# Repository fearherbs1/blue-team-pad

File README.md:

# blue-team-pad
An open source macropad for the cyber security analyst.

View the documentation for the Blue Team Pad by visiting: https://fearherbs1.github.io/blue-team-pad-docs/

Below is the demo unit that was shown at Champlain's 2023 ITS Capstone Showcase

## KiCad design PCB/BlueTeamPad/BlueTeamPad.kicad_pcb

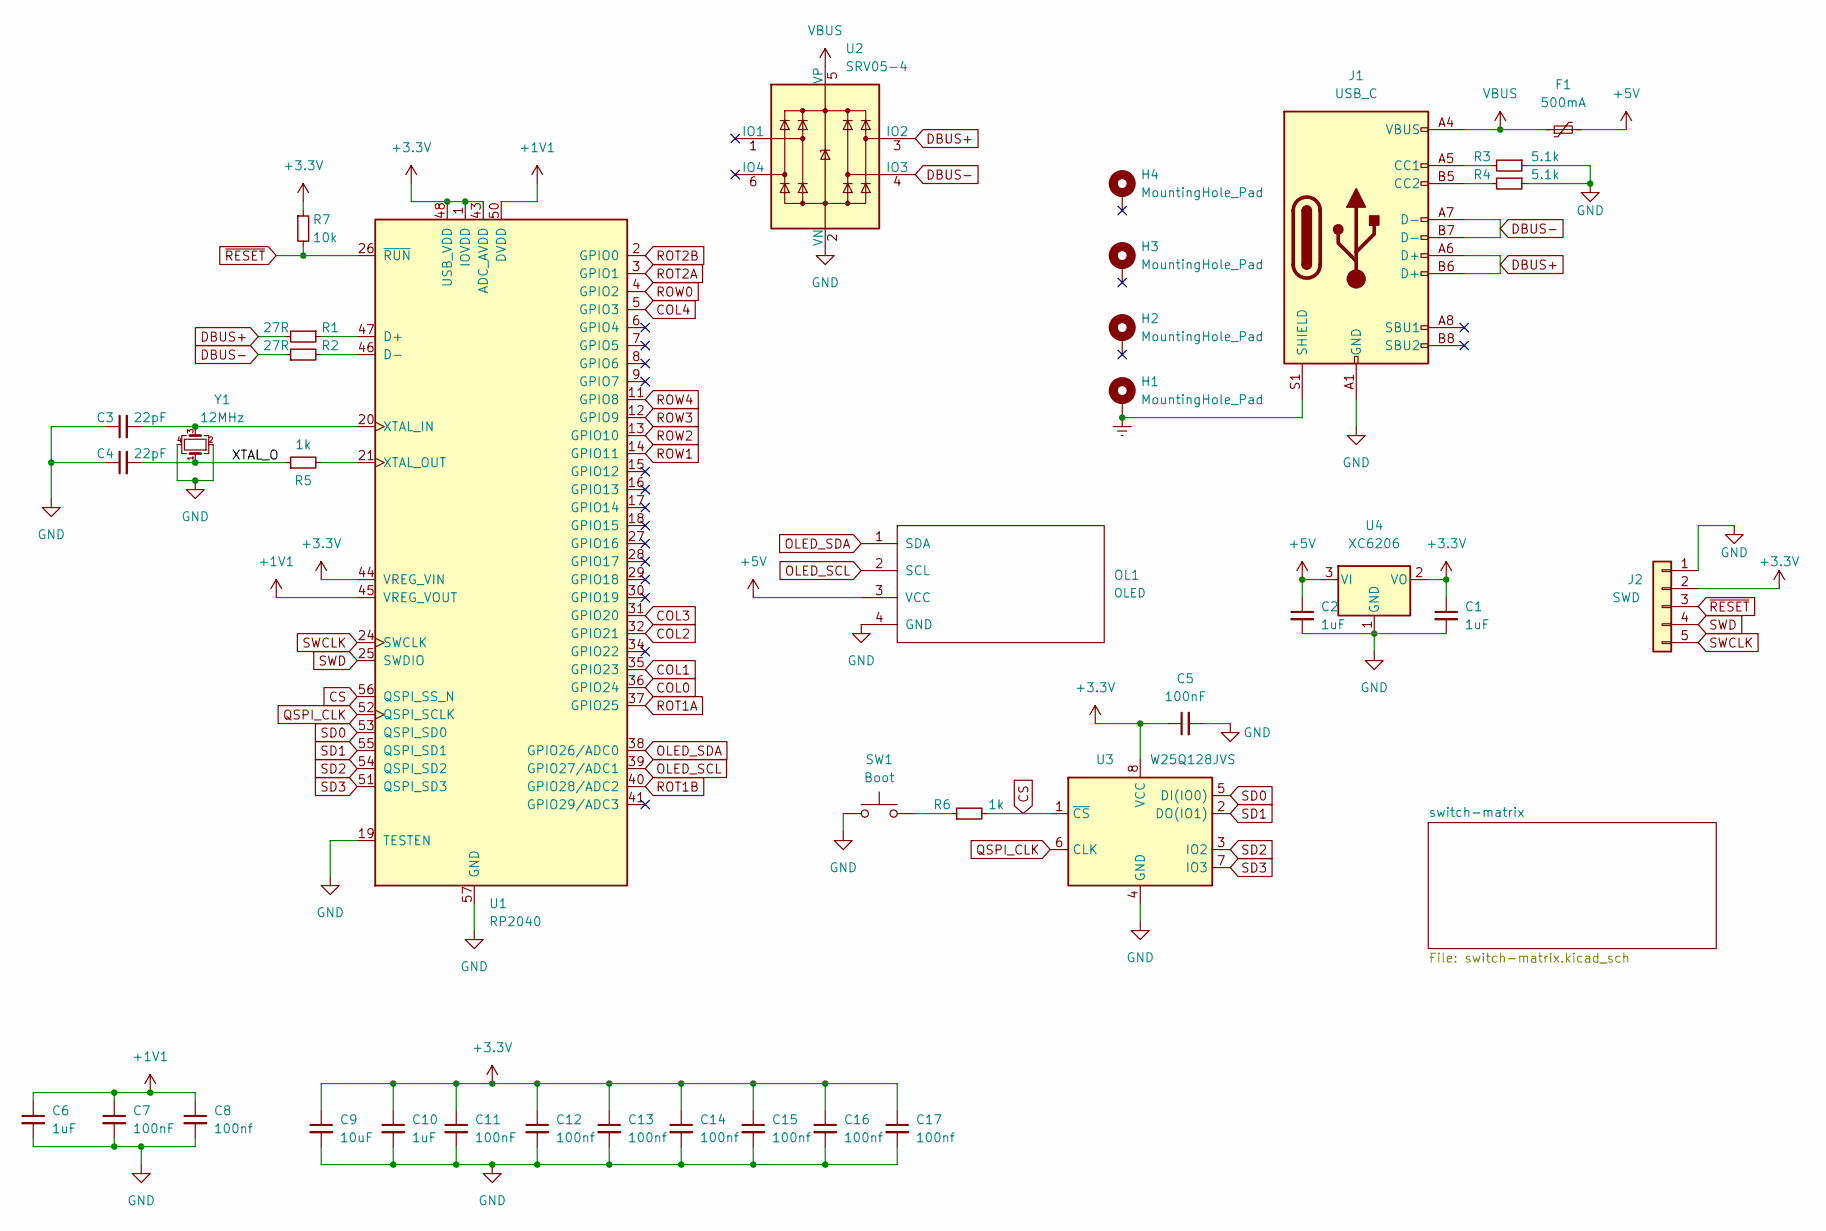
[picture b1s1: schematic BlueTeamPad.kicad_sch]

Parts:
C1, C2, C10: 1uF; C_0402_1005Metric; LCSC C52923
C3, C4: 22pF; C_0402_1005Metric; LCSC C1555
C5, C7, C11: 100nF; C_0402_1005Metric; LCSC C1525
C6: 1uF; C_0402_1005Metric
C8, C12, C13, C14, C15, C16, C17: 100nf; C_0402_1005Metric; LCSC C1525
C9: 10uF; C_0402_1005Metric; LCSC C15525
F1: 500mA; Fuse_1206_3216Metric; LCSC C70076
H1, H2, H3, H4: MountingHole_Pad; MountingHole_2.2mm_M2_Pad
J1: USB_C; USB_C_Receptacle_HRO_TYPE-C-31-M-12
J2: SWD; PinSocket_1x05_P2.54mm_Vertical
OL1: OLED; OLED_v2
R1, R2: 27R; R_0603_1608Metric; LCSC C25190
R3, R4: 5.1k; R_0402_1005Metric; LCSC C25905
R5, R6: 1k; R_0402_1005Metric; LCSC C11702
R7: 10k; R_0402_1005Metric; LCSC C25744
SW1: Boot; PinSocket_1x02_P2.54mm_Vertical
U1: RP2040; RP2040-QFN-56
U2: SRV05-4; SOT-23-6-routable; LCSC C85364
U3: W25Q128JVS; SOIC-8_5.23x5.23mm_P1.27mm; LCSC C97521
U4: XC6206; SOT-23; LCSC C5446
Y1: 12MHz; Crystal_SMD_3225-4Pin_3.2x2.5mm; LCSC C9002

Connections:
+1V1: C6.1, C7.1, C8.1, U1.23 (DVDD), U1.45 (VREG_VOUT), U1.50 (DVDD)
+3.3V: C1.1, C5.1, C9.1, C10.1, C11.1, C12.1, C13.1, C14.1, C15.1, C16.1, C17.1, J2.2, R7.1, U1.1 (IOVDD), U1.10 (IOVDD), U1.22 (IOVDD), U1.33 (IOVDD), U1.42 (IOVDD), U1.43 (ADC_AVDD), U1.44 (VREG_VIN), U1.48 (USB_VDD), U1.49 (IOVDD), U3.8 (VCC), U4.2 (VO)
+5V: C2.1, F1.2, OL1.3 (VCC), U4.3 (VI)
/XTAL_O: C4.2, R5.1, Y1.1
COL0: U1.36 (GPIO24); also elsewhere on the board
COL1: U1.35 (GPIO23); also elsewhere on the board
COL2: U1.32 (GPIO21); also elsewhere on the board
COL3: U1.31 (GPIO20); also elsewhere on the board
COL4: U1.5 (GPIO3); also elsewhere on the board
CS: R6.2, U1.56 (QSPI_SS_N), U3.1 (~CS)
DBUS+: J1.A6 (D+), J1.B6 (D+), R1.2, U2.3 (IO2)
DBUS-: J1.A7 (D-), J1.B7 (D-), R2.1, U2.4 (IO3)
Earth: H1.1, J1.S1 (SHIELD)
GND: C1.2, C2.2, C3.1, C4.1, C5.2, C6.2, C7.2, C8.2, C9.2, C10.2, C11.2, C12.2, C13.2, C14.2, C15.2, C16.2, C17.2, J1.A1 (GND), J1.A12 (GND), J1.B1 (GND), J1.B12 (GND), J2.1, OL1.4 (GND), R3.1, R4.1, SW1.1, U1.19 (TESTEN), U1.57 (GND), U2.2 (VN), U3.4 (GND), U4.1 (GND), Y1.2, Y1.4; also elsewhere on the board
unnamed: C3.2, U1.20 (XTAL_IN), Y1.3
unnamed: J1.A5 (CC1), R3.2
unnamed: J1.B5 (CC2), R4.2
unnamed: R1.1, U1.47 (D+)
unnamed: R2.2, U1.46 (D-)
unnamed: R5.2, U1.21 (XTAL_OUT)
unnamed: R6.1, SW1.2
OLED_SCL: OL1.2 (SCL), U1.39 (GPIO27/ADC1)
OLED_SDA: OL1.1 (SDA), U1.38 (GPIO26/ADC0)
QSPI_CLK: U1.52 (QSPI_SCLK), U3.6 (CLK)
ROT1A: U1.37 (GPIO25); also elsewhere on the board
ROT1B: U1.40 (GPIO28/ADC2); also elsewhere on the board
ROT2A: U1.3 (GPIO1); also elsewhere on the board
ROT2B: U1.2 (GPIO0); also elsewhere on the board
ROW0: U1.4 (GPIO2); also elsewhere on the board
ROW1: U1.14 (GPIO11); also elsewhere on the board
ROW2: U1.13 (GPIO10); also elsewhere on the board
ROW3: U1.12 (GPIO9); also elsewhere on the board
ROW4: U1.11 (GPIO8); also elsewhere on the board
SD0: U1.53 (QSPI_SD0), U3.5 (DI(IO0))
SD1: U1.55 (QSPI_SD1), U3.2 (DO(IO1))
SD2: U1.54 (QSPI_SD2), U3.3 (IO2)
SD3: U1.51 (QSPI_SD3), U3.7 (IO3)
SWCLK: J2.5, U1.24 (SWCLK)
SWD: J2.4, U1.25 (SWDIO)
VBUS: F1.1, J1.A4 (VBUS), J1.A9 (VBUS), J1.B4 (VBUS), J1.B9 (VBUS), U2.5 (VP)
~RESET: J2.3, R7.2, U1.26 (~RUN)

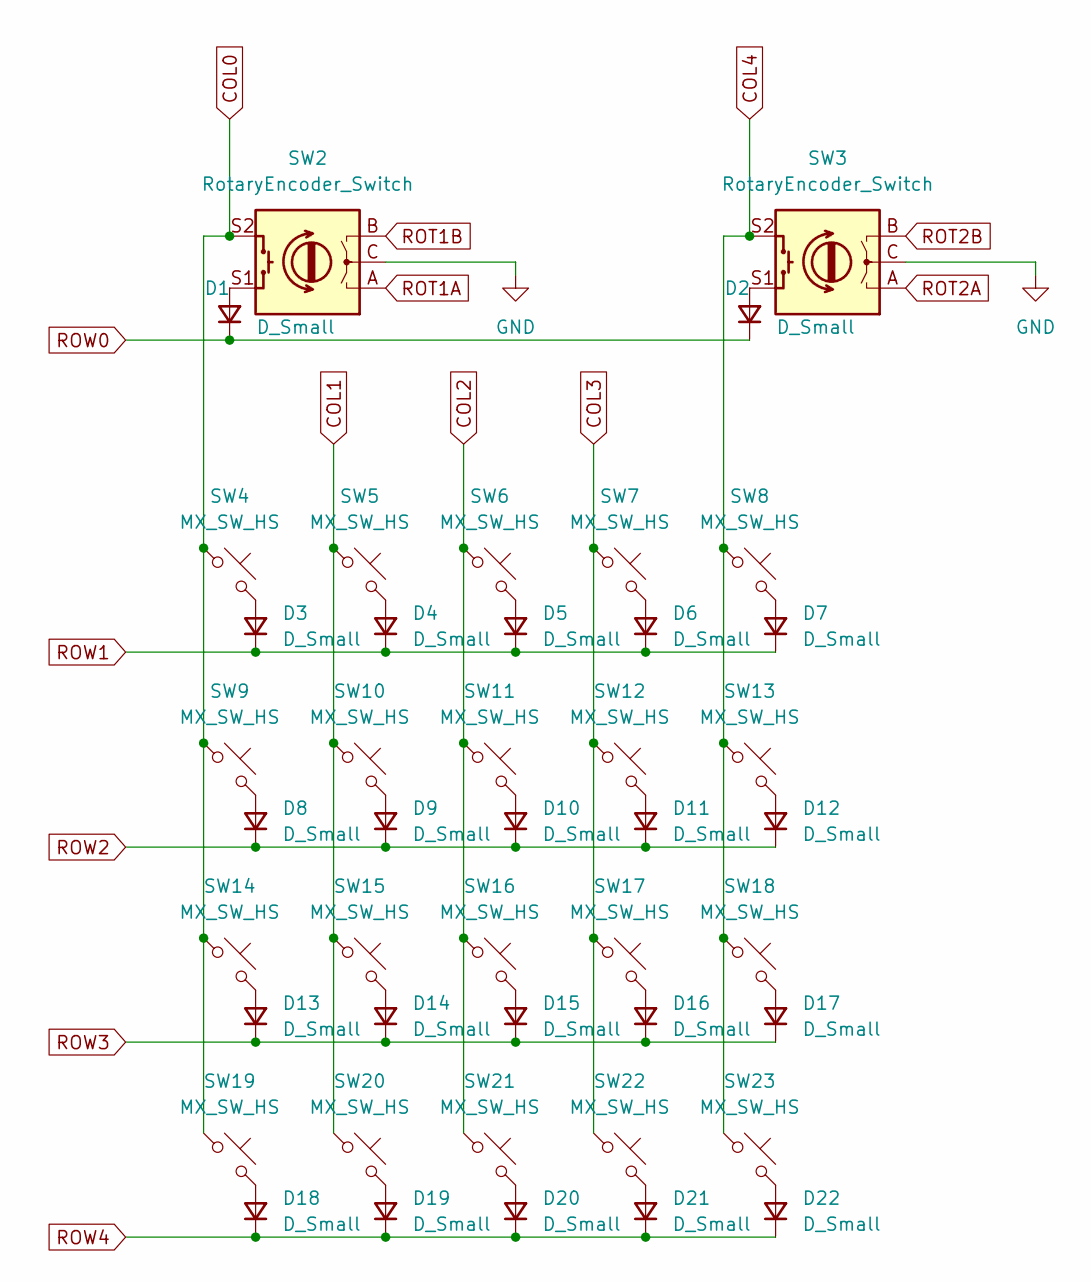
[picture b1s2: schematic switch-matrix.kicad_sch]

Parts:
D1, D2, D3, D4, D5, D6, D7, D8, D9, D10, D11, D12, D13, D14, D15, D16, D17, D18, D19, D20, D21, D22: D_Small; D_SOD-123; LCSC C81598
SW2, SW3: RotaryEncoder_Switch; ROT_Alps_EC11E-Switch
SW4, SW5, SW6, SW7, SW8, SW9, SW10, SW11, SW12, SW13, SW14, SW15, SW16, SW17, SW18, SW19, SW20, SW21, SW22, SW23: MX_SW_HS; SW_MX_HS_1u

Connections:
COL0: SW2.S2, SW4.1, SW9.1, SW14.1, SW19.1; also elsewhere on the board
COL1: SW5.1, SW10.1, SW15.1, SW20.1; also elsewhere on the board
COL2: SW6.1, SW11.1, SW16.1, SW21.1; also elsewhere on the board
COL3: SW7.1, SW12.1, SW17.1, SW22.1; also elsewhere on the board
COL4: SW3.S2, SW8.1, SW13.1, SW18.1, SW23.1; also elsewhere on the board
GND: SW2.C, SW3.C; also elsewhere on the board
unnamed: D1.2 (A), SW2.S1
unnamed: D2.2 (A), SW3.S1
unnamed: D3.2 (A), SW4.2
unnamed: D4.2 (A), SW5.2
unnamed: D5.2 (A), SW6.2
unnamed: D6.2 (A), SW7.2
unnamed: D7.2 (A), SW8.2
unnamed: D8.2 (A), SW9.2
unnamed: D9.2 (A), SW10.2
unnamed: D10.2 (A), SW11.2
unnamed: D11.2 (A), SW12.2
unnamed: D12.2 (A), SW13.2
unnamed: D13.2 (A), SW14.2
unnamed: D14.2 (A), SW15.2
unnamed: D15.2 (A), SW16.2
unnamed: D16.2 (A), SW17.2
unnamed: D17.2 (A), SW18.2
unnamed: D18.2 (A), SW19.2
unnamed: D19.2 (A), SW20.2
unnamed: D20.2 (A), SW21.2
unnamed: D21.2 (A), SW22.2
unnamed: D22.2 (A), SW23.2
ROT1A: SW2.A; also elsewhere on the board
ROT1B: SW2.B; also elsewhere on the board
ROT2A: SW3.A; also elsewhere on the board
ROT2B: SW3.B; also elsewhere on the board
ROW0: D1.1 (K), D2.1 (K); also elsewhere on the board
ROW1: D3.1 (K), D4.1 (K), D5.1 (K), D6.1 (K), D7.1 (K); also elsewhere on the board
ROW2: D8.1 (K), D9.1 (K), D10.1 (K), D11.1 (K), D12.1 (K); also elsewhere on the board
ROW3: D13.1 (K), D14.1 (K), D15.1 (K), D16.1 (K), D17.1 (K); also elsewhere on the board
ROW4: D18.1 (K), D19.1 (K), D20.1 (K), D21.1 (K), D22.1 (K); also elsewhere on the board

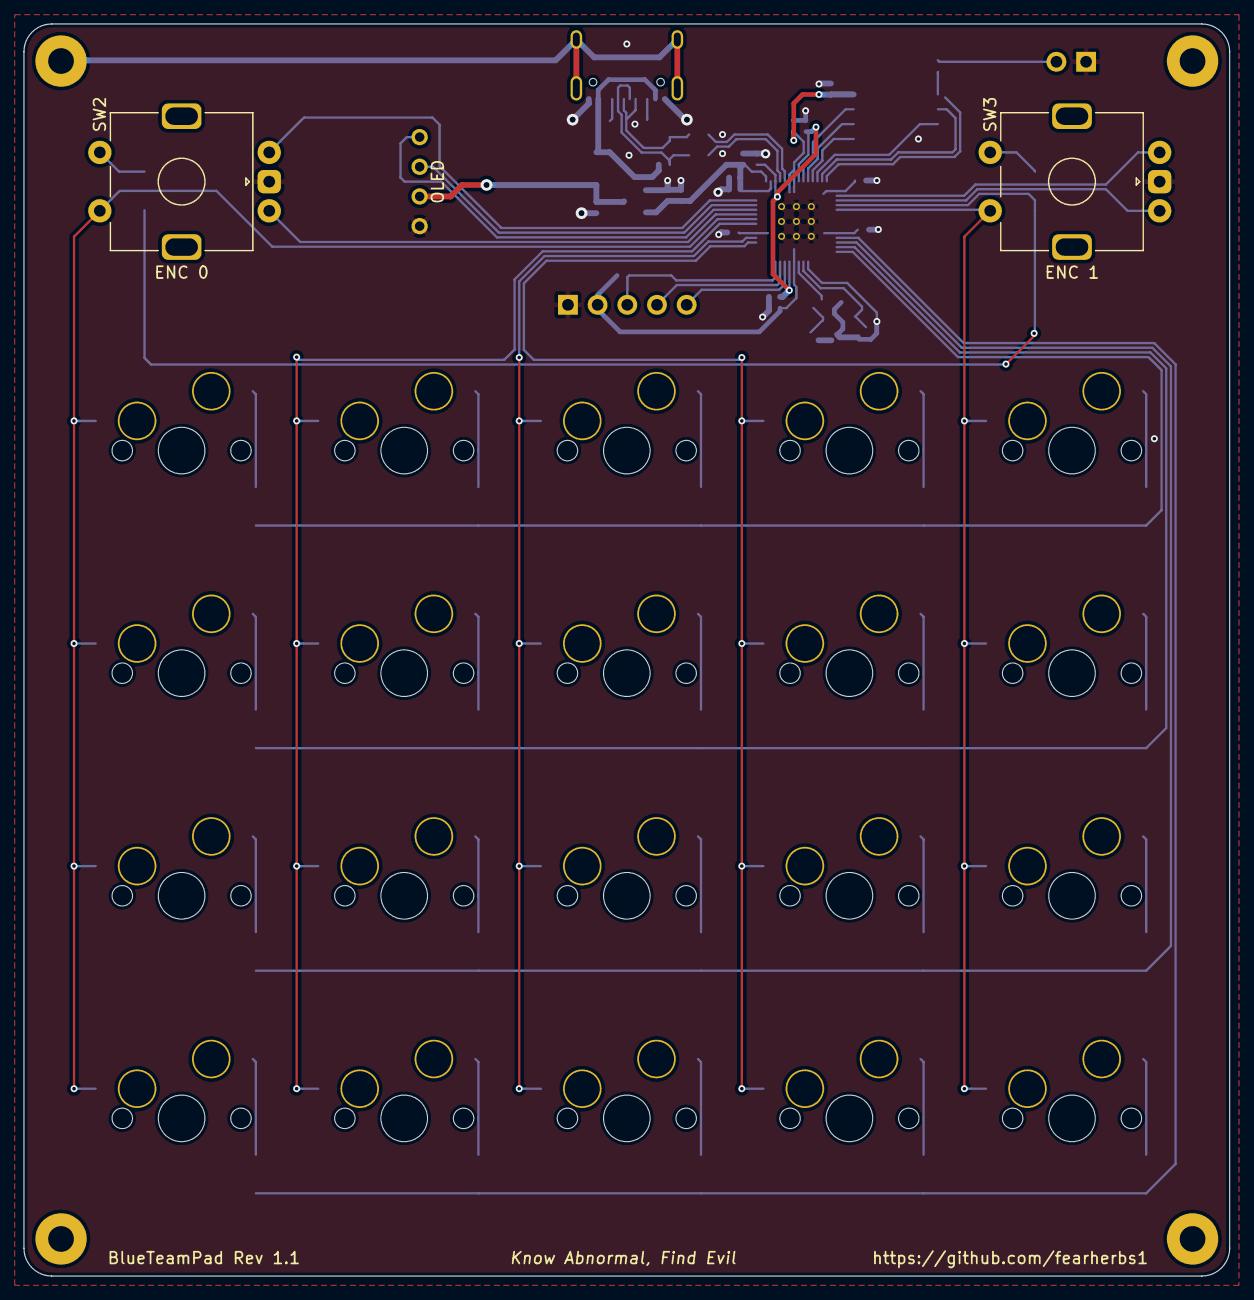
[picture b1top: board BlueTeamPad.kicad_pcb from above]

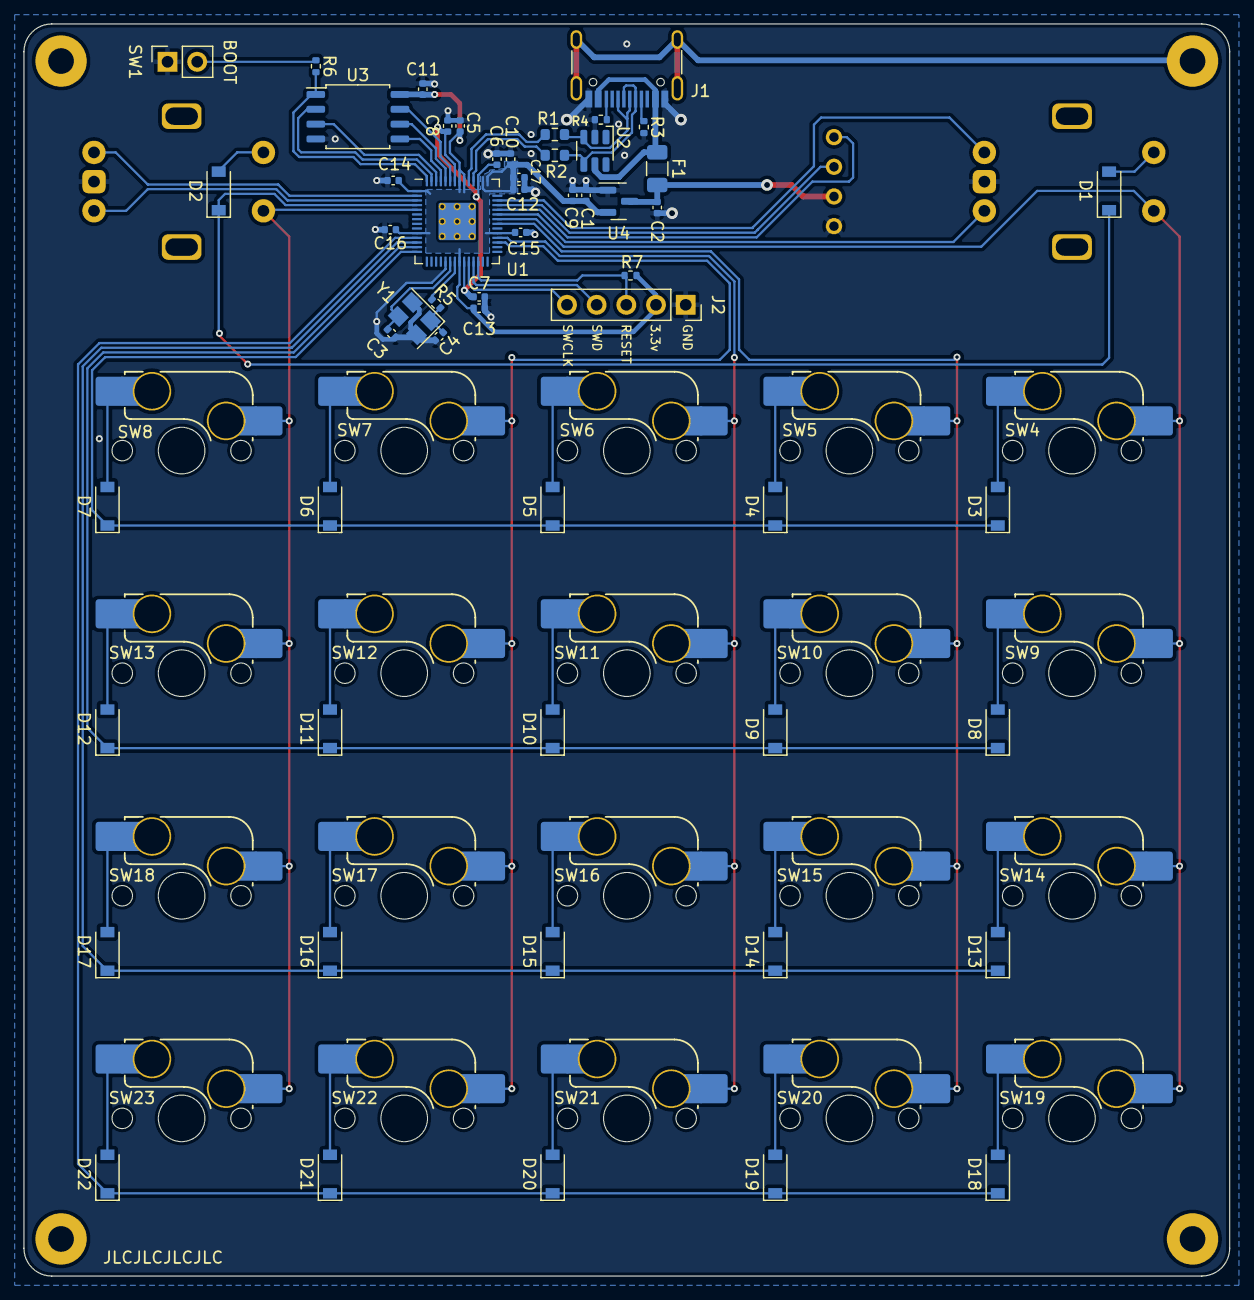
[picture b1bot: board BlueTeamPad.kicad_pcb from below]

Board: 2 copper layers, 103.2 x 107.2 mm, 82 parts (75 on the bottom side), 63 nets.

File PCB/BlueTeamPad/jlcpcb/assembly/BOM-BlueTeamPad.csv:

Comment,Designator,Footprint,LCSC
1k,"R5,R6",R_0402_1005Metric,C11702
100nF,"C11,C12,C13,C14,C15,C16,C17,C5,C7,C8",C_0402_1005Metric,C1525
10uF,C9,C_0402_1005Metric,C15525
22pF,"C3,C4",C_0402_1005Metric,C1555
USB_C,J1,USB_C_Receptacle_HRO_TYPE-C-31-M-12,C165948
RP2040,U1,RP2040-QFN-56,C2040
27R,"R1,R2",R_0603_1608Metric,C25190
10k,R7,R_0402_1005Metric,C25744
5.1k,"R3,R4",R_0402_1005Metric,C25905
1uF,"C1,C10,C2,C6",C_0402_1005Metric,C52923
XC6206,U4,SOT-23,C5446
500mA,F1,Fuse_1206_3216Metric,C70076
D_Small,"D1,D10,D11,D12,D13,D14,D15,D16,D17,D18,D19,D2,D20,D21,D22,D3,D4,D5,D6,D7,D8,D9",D_SOD-123,C81598
SRV05-4,U2,SOT-23-6-routable,C85364
12MHz,Y1,Crystal_SMD_3225-4Pin_3.2x2.5mm,C9002
W25Q128JVS,U3,SOIC-8_5.23x5.23mm_P1.27mm,C97521
MountingHole_Pad,H2,MountingHole_2.2mm_M2_Pad,
OLED,OL1,OLED_v2,
MountingHole_Pad,H1,MountingHole_2.2mm_M2_Pad,
RotaryEncoder_Switch,SW3,ROT_Alps_EC11E-Switch,
MountingHole_Pad,H3,MountingHole_2.2mm_M2_Pad,
MountingHole_Pad,H4,MountingHole_2.2mm_M2_Pad,
RotaryEncoder_Switch,SW2,ROT_Alps_EC11E-Switch,
MX_SW_HS,SW20,SW_MX_HS_1u,
MX_SW_HS,SW5,SW_MX_HS_1u,
Boot,SW1,PinSocket_1x02_P2.54mm_Vertical,
MX_SW_HS,SW6,SW_MX_HS_1u,
MX_SW_HS,SW21,SW_MX_HS_1u,
MX_SW_HS,SW22,SW_MX_HS_1u,
MX_SW_HS,SW13,SW_MX_HS_1u,
MX_SW_HS,SW18,SW_MX_HS_1u,
MX_SW_HS,SW16,SW_MX_HS_1u,
MX_SW_HS,SW11,SW_MX_HS_1u,
MX_SW_HS,SW12,SW_MX_HS_1u,
MX_SW_HS,SW9,SW_MX_HS_1u,
MX_SW_HS,SW10,SW_MX_HS_1u,
MX_SW_HS,SW7,SW_MX_HS_1u,
MX_SW_HS,SW15,SW_MX_HS_1u,
MX_SW_HS,SW4,SW_MX_HS_1u,
MX_SW_HS,SW8,SW_MX_HS_1u,
MX_SW_HS,SW23,SW_MX_HS_1u,
MX_SW_HS,SW19,SW_MX_HS_1u,
MX_SW_HS,SW14,SW_MX_HS_1u,
MX_SW_HS,SW17,SW_MX_HS_1u,

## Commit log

2023-02-11 Initial File Add
2023-02-11 add photo
2023-02-27 Update to Current
2023-04-10 Add Relegendable Templates
